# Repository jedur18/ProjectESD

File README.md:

# ESD project
**Project:** Motion Sensor Alarm (Group 2)
General Description: This project is divided in two groups. Group 1 will work with the motion sensor and will transmit a signal to the cloud when alarm is activated. Group 2 will work with the buzzer, display and keyboard in order to introduce the code to switch the alarm off.

**Group 2 description:** Our system will recive the signal of the activated alarm from the cloud by the LORA module. The idea then is to activate the buzzer to emit the sound. While the alarm is ringing the user will be able to introduce a secret code using the keyboard to switch the alarm off. In the display it will be showed the status of the system (Alarm ON/OFF), the code introduced and if it is correct or not.

**Distribution of the work:**
- EDU:
  - Basic part:
    - Numeric Keyboard: With this part digital I/O will be faced. I will also need to remove the bouncing of the buttons, deal with PCINTs (Pin change interruptions).
  - Individual Goals to reach 4/5 mark:
    - Display: SPI communication. Showing the system state, the code introduced by the user and if the code is correct or not.
    - Software protection--> Encryption. Asymmetric encryption if its possible (need to investigate on it)

- ALI:
  - basic part:
    - Buzzer: sendig out sound by the PWM signals as the LEDs.
    - LEDs control. Green:normal mode. Red:alarm mode. (LED blinking-->PWM)
  - More advansed part for us electronic backgrounded students is software development:
    - We are going to make the keypad unit and the sensor unit works as front end which will communicate to the back end server.
    - We are even going to make it possible for the system to be able to support more than one sensor and make it possibble for the master to identify which unit is detecting motions.

## EQUIPMENT:
- Murata CMWX1ZZABZLoRa Module:
	Datasheet:https://wireless.murata.com/datasheet?/RFM/data/type_abz.pdf
  - STM32L0x2:
		Documentation (Full information about micro): https://www.ece.uvic.ca/~ece355/lab/supplement/stm32f0RefManual.pdf
		With rust: https://docs.rs/stm32f0x2/0.1.0/stm32f0x2/

- Oled Display: SSD1306. 
	Datasheet: https://buildmedia.readthedocs.org/media/pdf/ssd1306/latest/ssd1306.pdf
	Website to order: https://cdon.se/hem-tradgard/oled-display-0-96-tum-med-128x64-vita-pixlar-i2c-ssd1306-p50542494
	Prize: 59kr
- Driver for Oled Display SSD1306
	Datasheet: https://cdn-shop.adafruit.com/datasheets/SSD1306.pdf
- LEDs: (Maybe available at lab)
	Red LED: https://se.rs-online.com/web/p/leds/2285988/
	Green LED: https://se.rs-online.com/web/p/leds/2286004/
- Numeric Keyboard:
	Website to order: https://www.elfa.se/en/3x4-matrix-keypad-adafruit-3845/p/30139179?queryFromSuggest=true
	Prize: 61.90kr
	Documentation: https://www.adafruit.com/product/1824
					https://www.futurlec.com/Keypad3x4.shtml
					Arduino libraries and documentation: https://playground.arduino.cc/Code/Keypad/
- Capacitors:
	6x100nF for decoupling: 
			for power supply:

- Resistors: 
	2x10k for pull Up and pull Down resistors for NRST and BOOT0: https://www.elfa.se/en/thick-film-smd-resistor-0805-10kohm-125mw-rnd-components-rnd-1550805s8f1002t5e/p/30056718?q=10k+resistor+0805&pos=1&origPos=1&origPageSize=10&track=true
	Prize: 0.4972 (ordering 4)
	for power supply: 
	
- Serial Wire Debug (SWD) to program and debug the MCU: 
	Website to oder: https://www.elfa.se/en/ampmodu-mod-ii-straight-male-pcb-header-through-hole-54mm-te-connectivity-826629/p/14371639?q=straight+male+pcb+header&pos=3&origPos=97&origPageSize=10&track=true
	Prize: 5.78SEK
	Datasheet:https://www.elfa.se/Web/Downloads/_t/ds/8266xx_x_eng_tds.pdf?pid=14371639

- Power Supply:

- Buzzer: 
  - piezo buzzer (KMTG1603-1) : https://se.rs-online.com/web/p/piezo-buzzer-components/7675349/?relevancy-data=636F3D3126696E3D4931384E53656172636847656E65726963266C753D7376266D6D3D6D61746368616C6C7061727469616C26706D3D5E5B5C707B4C7D5C707B4E647D2D2C2F255C2E5D2B2426706F3D31333326736E3D592673723D2673743D4B4559574F52445F53494E474C455F414C5048415F4E554D455249432673633D592677633D4E4F4E45267573743D4B4D5447313630332D31267374613D4B4D5447313630332D3126&searchHistory=%7B%22enabled%22%3Atrue%7D
    - Datasheet: https://docs.rs-online.com/aa51/0900766b81113b92.pdf
  - Transistor: (MMBT2222A)
    - Datasheet: https://www.elfa.se/Web/Downloads/_p/df/Diotec-MMBT2222A_eng_ger_tds.pdf?pid=30146837

 - num-pad:
   - Rectifier Diodes: https://www.elfa.se/en/rectifier-diode-1206-taiwan-semiconductor-ts4148-rxg/p/30139387?q=rectifier+diodes&pos=1&origPos=265&origPageSize=10&track=true
     - Datasheet: https://www.elfa.se/Web/Downloads/_t/ds/TS4148_RXG_eng_tds.pdf?pid=30139387
   - Buttons:
     - RND210-00204: https://www.elfa.se/en/pcb-tactile-switch-210-1no-57n-6mm-rnd-components-rnd-210-00204/p/30090660?q=Tactile+Switch&pos=5&origPos=16&origPageSize=10&track=true
     - Datasheet: https://www.elfa.se/Web/Downloads/_t/ds/RND%20210-00204_eng_tds.pdf?pid=30090660
   
 - Antenn con: https://www.elfa.se/en/micro-coaxial-straight-socket-micro-coaxial-connector-50ohm-6ghz-molex-73412-0110/p/30076410?queryFromSuggest=true
   - datasheet: https://www.elfa.se/Web/Downloads/_t/ds/73412-0110_eng_tds.pdf?pid=30076410
   
 - Micro-USB B connector: https://www.elfa.se/en/socket-micro-usb-smd-wuerth-elektronik-629105150521/p/30009163?q=micro+usb+smd&pos=4&origPos=4&origPageSize=10&track=true
   - Datasheet: https://www.elfa.se/Web/Downloads/40/32/629105150521.pdf?pid=30009163
   
 - Voltage Regulator:
   - LM1117ADJ: https://www.elfa.se/en/ldo-voltage-regulator-800ma-sot-223-texas-instruments-lm1117impx-adj-nopb/p/30019194?queryFromSuggest=true
   
 - LEDs:
   - Red:https://www.elfa.se/en/smd-led-640nm-1206-600mcd-30ma-kingbright-kptd-3216surc/p/17531032?q=*&pos=3&origPos=3&origPageSize=10&track=true
     - Datasheet: https://www.elfa.se/Web/Downloads/6_/en/csKingbright_SMD-LED-rot-KTPD3216_EN.pdf?pid=17531032
   - Green: https://www.elfa.se/en/smd-led-468nm-1206-700mcd-20ma-kingbright-kptd-3216qbc/p/17510753?q=*&pos=1&origPos=1&origPageSize=10&track=true
     - Datasheet: https://www.elfa.se/Web/Downloads/_t/ds/kptd-3216qbc-d_eng_tds.pdf?pid=17510753

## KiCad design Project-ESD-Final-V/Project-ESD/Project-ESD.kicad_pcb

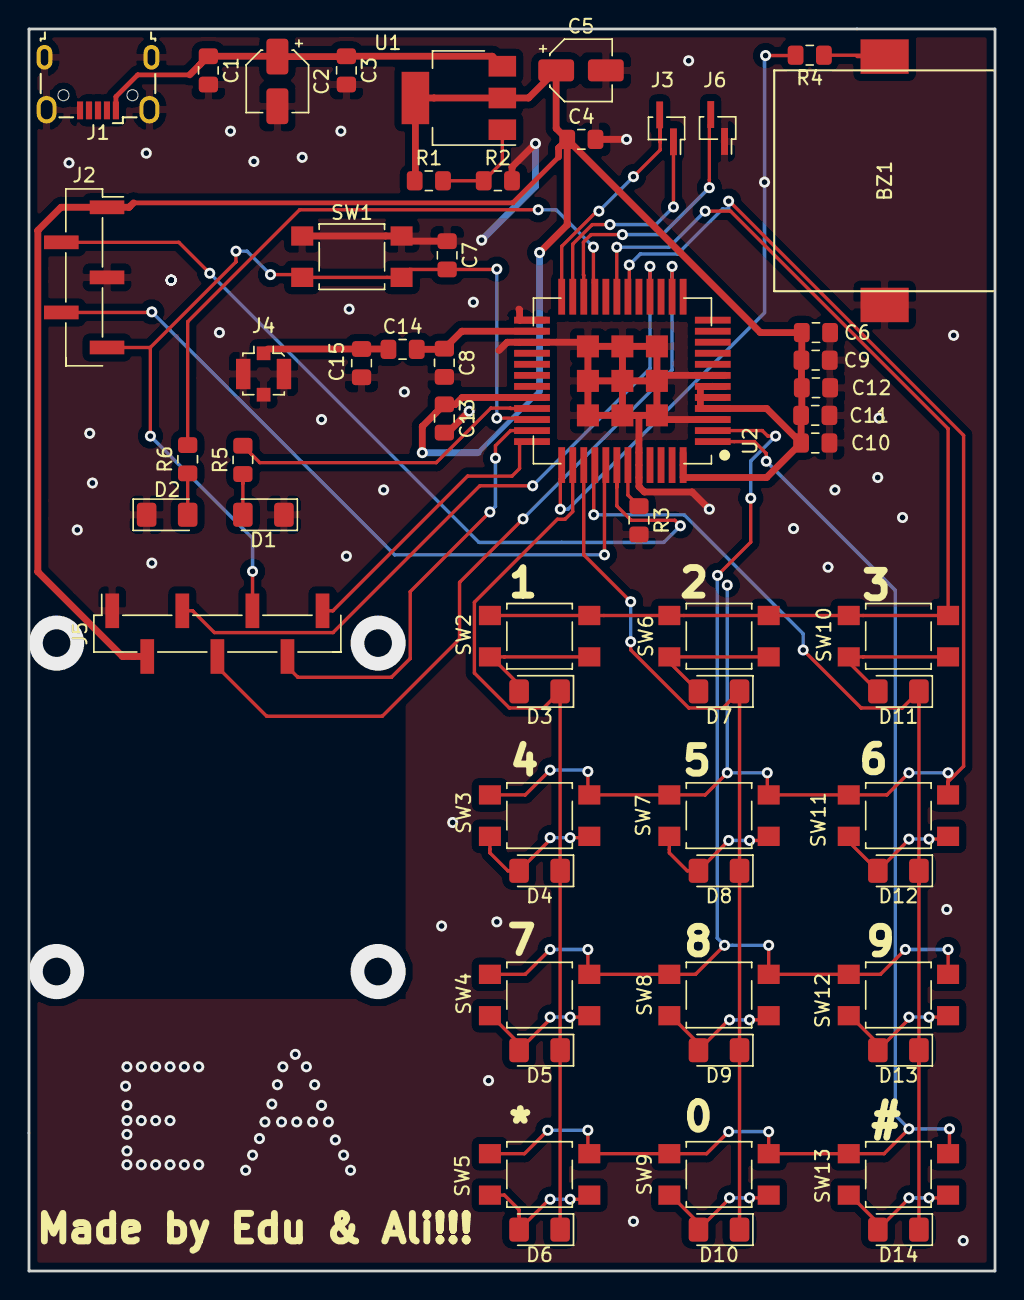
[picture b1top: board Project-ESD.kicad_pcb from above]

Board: 2 copper layers, 70.0 x 90.0 mm, 57 parts (0 on the bottom side), 42 nets.

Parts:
BZ1: Buzzer; kmtg1603-1
C1, C3, C4, C7, C8, C15: 100n; C_0805_2012Metric_Pad1.15x1.40mm_HandSolder
C2, C5: 10u; CP_Elec_4x5.4
C6, C10: 10uF; C_0805_2012Metric_Pad1.15x1.40mm_HandSolder
C9, C13: 1uF; C_0805_2012Metric_Pad1.15x1.40mm_HandSolder
C11, C12: 0.1uF; C_0805_2012Metric_Pad1.15x1.40mm_HandSolder
C14: 100p; C_0805_2012Metric_Pad1.15x1.40mm_HandSolder
D1, D2: LED; LED_1206_3216Metric_Pad1.42x1.75mm_HandSolder
D3, D4, D5, D6, D7, D8, D9, D10, D11, D12, D13, D14: D; D_1206_3216Metric_Pad1.42x1.75mm_HandSolder
J1: USB_OTG; USB_Micro-B_Wuerth_629105150521
J2: Conn_01x05_Male; PinHeader_1x05_P2.54mm_Vertical_SMD_Pin1Right
J3, J6: Conn_01x02_Female; PinSocket_1x02_P1.00mm_Vertical_SMD_Pin1Right
J4: Conn_Coaxial; U.FL_Molex_MCRF_73412-0110_Vertical
J5: Conn_01x07_Male; PinHeader_1x07_P2.54mm_Vertical_SMD_Pin1Right
R1: 3.3k; R_0805_2012Metric_Pad1.15x1.40mm_HandSolder
R2: 6.8k; R_0805_2012Metric_Pad1.15x1.40mm_HandSolder
R3: 10k; R_0805_2012Metric_Pad1.15x1.40mm_HandSolder
R4: 680; R_0805_2012Metric_Pad1.15x1.40mm_HandSolder
R5, R6: 330; R_0805_2012Metric_Pad1.15x1.40mm_HandSolder
SW1, SW2, SW3, SW4, SW5, SW6, SW7, SW8, SW9, SW10, SW11, SW12, SW13: SW_Push; SW_SPST_TL3305C
U1: LM1117ADJ; SOT-223
U2: CMWX1ZZABZ-078; CMWX1ZZABZ_longer_pads

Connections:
+3V3: C4.1, C5.1, C6.1, C9.1, C10.1, C11.1, C12.1, C13.1, J2.1, J5.2, R1.1, U1.2, U1.4, U2.4, U2.5, U2.6, U2.32, U2.48
+5V: C1.1, C2.1, C3.1, J1.1, U1.3
BZ: R4.2, U2.37
COL1: D3.1, D4.1, D5.1, D6.1, U2.38
COL2: D7.1, D8.1, D9.1, D10.1, U2.39
COL3: D11.1, D12.1, D13.1, D14.1, U2.40
CS: J5.7, U2.36
D0: J5.3, U2.16
D1: J5.4, U2.14
DC: J5.6, U2.35
GND: BZ1.2, C1.2, C2.2, C3.2, C4.2, C5.2, C6.2, C7.1, C8.2, C9.2, C10.2, C11.2, C12.2, C13.2, C15.2, D1.1, D2.1, J1.5, J1.6, J2.3, J4.2, J5.1, J6.1, R2.2, R3.2, SW1.1, U2.3, U2.7, U2.25, U2.27, U2.44, U2.49, U2.50, U2.51, U2.52, U2.53, U2.54, U2.55, U2.56, U2.57
LED1: R5.2, U2.33
LED2: R6.2, U2.21
unnamed: BZ1.1, R4.1
unnamed: C14.1, C15.1, J4.1
unnamed: C8.1, C14.2, U2.26
unnamed: D1.2, R5.1
unnamed: D2.2, R6.1
unnamed: D3.2, SW2.2
unnamed: D4.2, SW3.2
unnamed: D5.2, SW4.2
unnamed: D6.2, SW5.2
unnamed: D7.2, SW6.2
unnamed: D8.2, SW7.2
unnamed: D9.2, SW8.2
unnamed: D10.2, SW9.2
unnamed: D11.2, SW10.2
unnamed: D12.2, SW11.2
unnamed: D13.2, SW12.2
unnamed: D14.2, SW13.2
unnamed: J2.2, U2.42
unnamed: J2.4, U2.41
unnamed: J3.1, U2.23
unnamed: J3.2, U2.24
unnamed: J6.2, U2.22
unnamed: R1.2, R2.1, U1.1
unnamed: R3.1, U2.43
RES: C7.2, J2.5, J5.5, SW1.2, U2.34
ROW1: SW2.1, SW6.1, SW10.1, U2.19
ROW2: SW3.1, SW7.1, SW11.1, U2.18
ROW3: SW4.1, SW8.1, SW12.1, U2.2
ROW4: SW5.1, SW9.1, SW13.1, U2.1

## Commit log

2020-01-30 README.md
    Update
2020-01-30 Encryption try
    I will just update a file encrypted
2020-01-30 Update README.md
    Introduce part of my components
2020-01-31 Update README.md
    Adding more components and documentation
2020-01-31 Update README.md
    More components
2020-02-07 Update
    Pinlayout
    Kicad first version
2020-02-10 Schemaitc update
    Add: SWD connector, SPI connections, antenna
2020-02-11 Update of schematic
2020-02-11 Schematic update
2020-02-12 Final Update Of PCB
    The grb files will come soon...
2020-02-13 Final verson 2
2020-02-13 Final verson with the gerber files(Final Verson 3)
2020-02-13 Final with correct Gerber files, (final Verson 4)
2020-03-19 Commit of the initial folder for the project. It contains working files for controlling LEDs and for controlling the buttons(wihtout interruptions). It also have the first version of PWM using LPTIME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
2020-04-03 This commit with add all the software part working. On the one hand it contain the four code files which contain pwm,adc,serial and gpio functionalitis (the minimun requirements for the project). For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
